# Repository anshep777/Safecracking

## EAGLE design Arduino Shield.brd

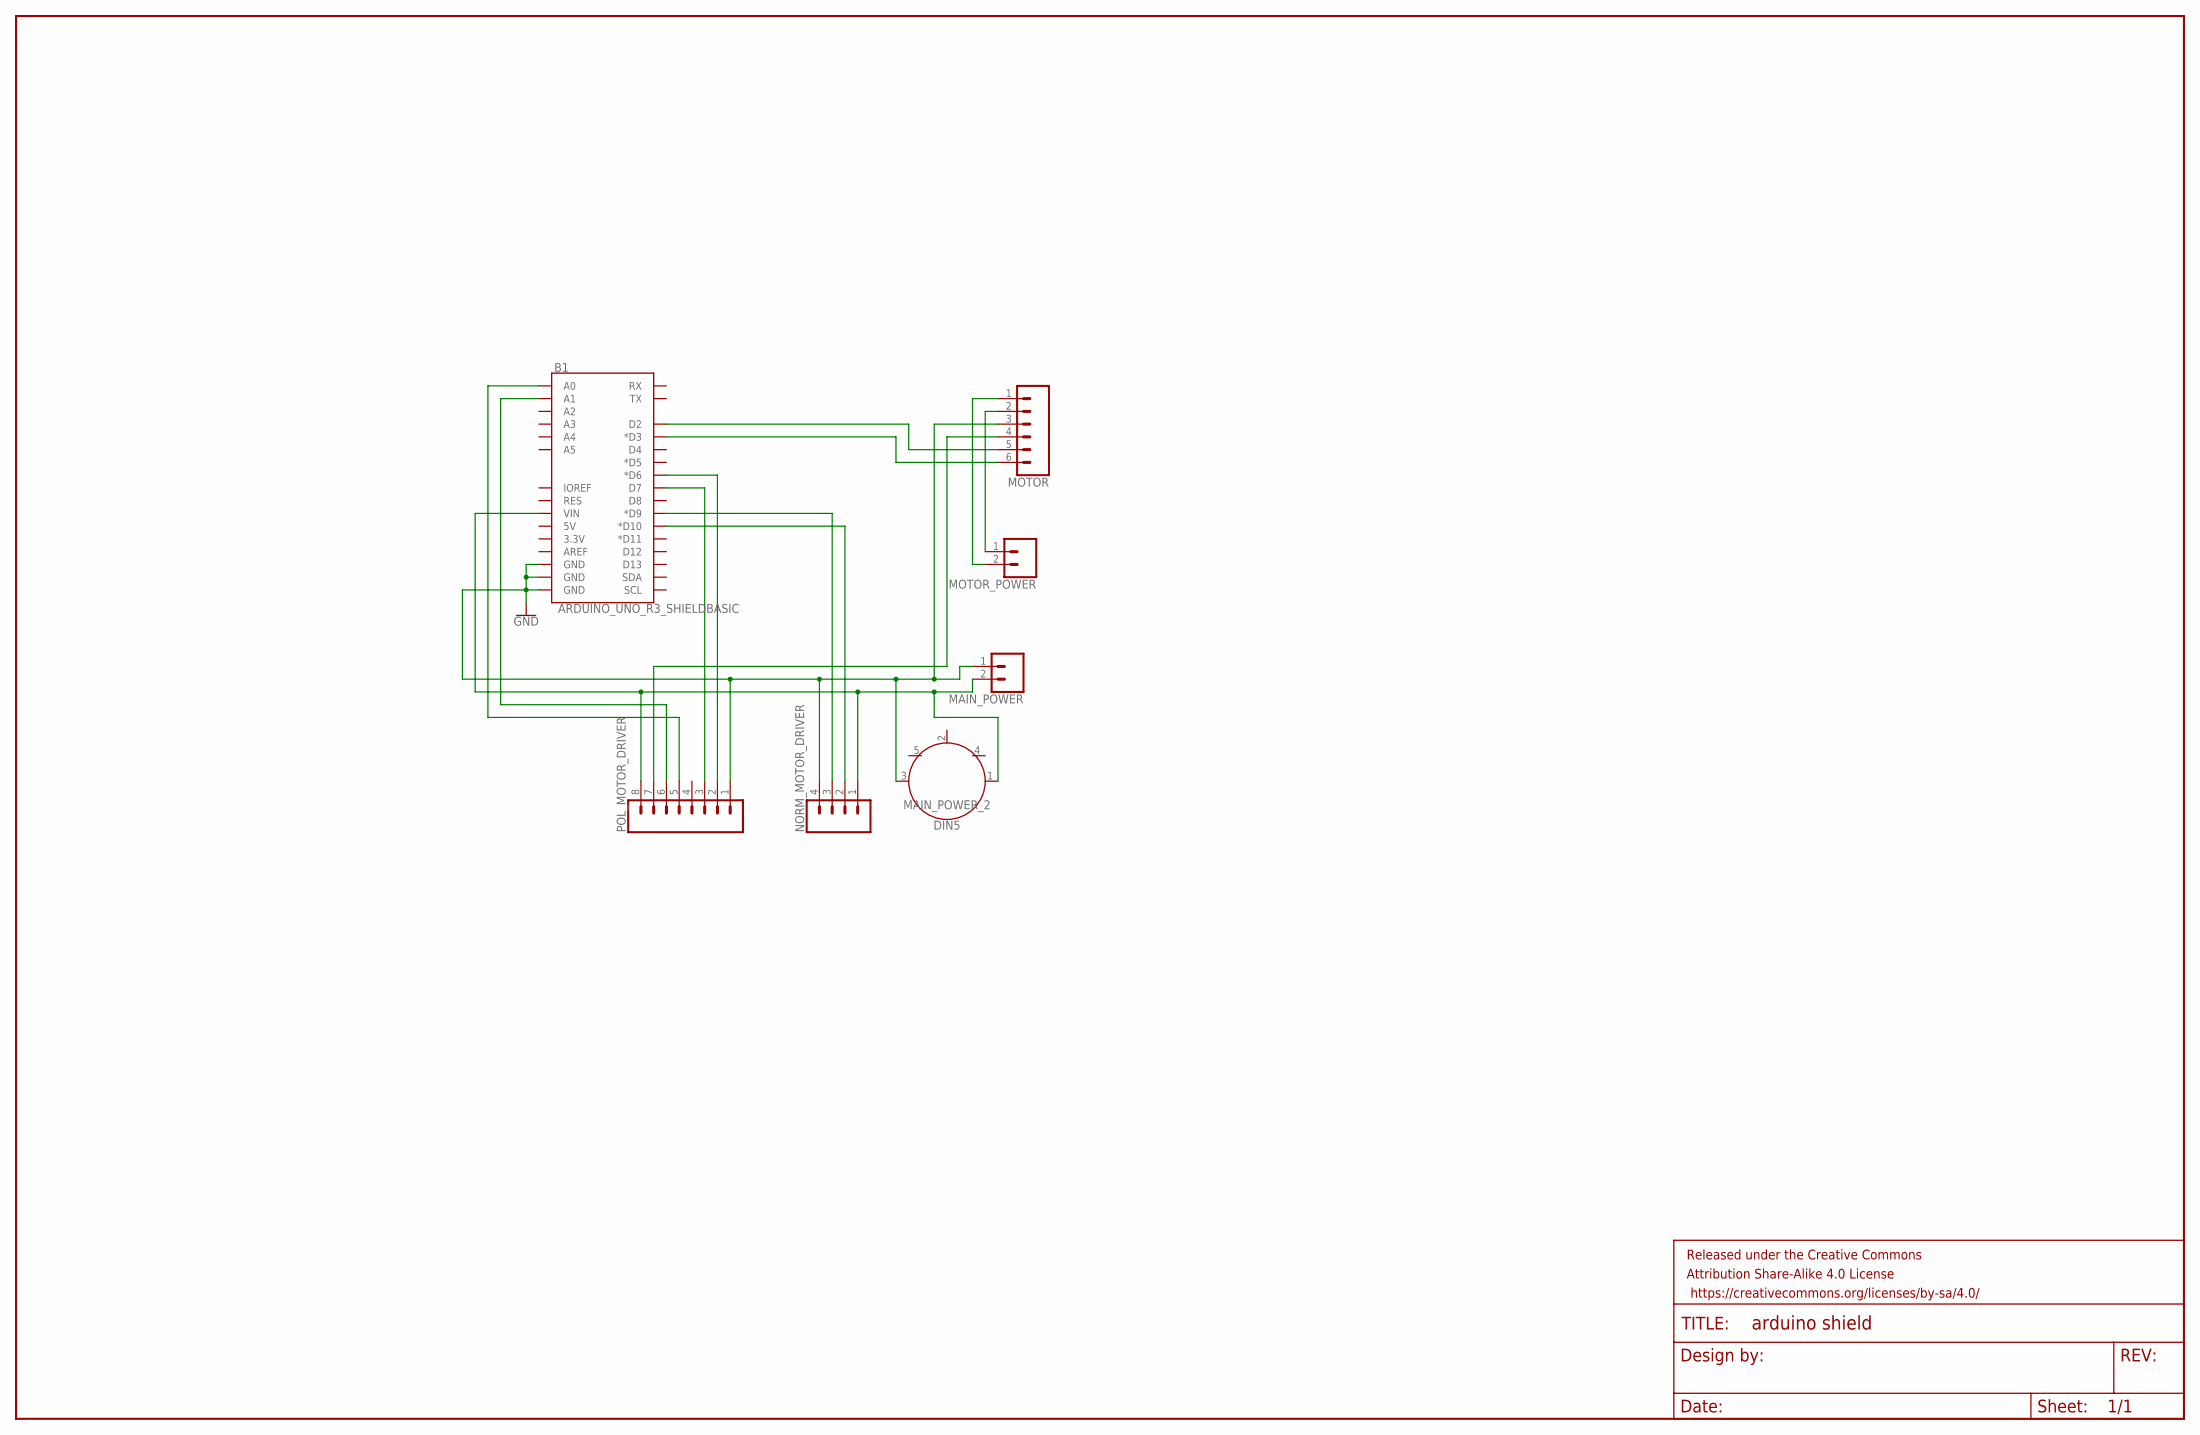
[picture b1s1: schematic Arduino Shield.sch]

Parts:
B1: ARDUINO_UNO_R3_SHIELDBASIC; UNO_R3_SHIELD
FRAME1: FRAME-LEDGER; CREATIVE_COMMONS
MAIN_POWER: CONN_02-JST-2-PTH-NO_SILK; JST-2-PTH-NS
MAIN_POWER_2: DIN5; DIN5-RA-PTH
MOTOR: CONN_06SILK_FEMALE_PTH; 1X06
MOTOR_POWER: CONN_02-JST-2-PTH-NO_SILK; JST-2-PTH-NS
NORM_MOTOR_DRIVER: CONN_04JST-PTH; JST-4-PTH
POL_MOTOR_DRIVER: CONN_08"; 1X08

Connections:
GND: B1.GND@0 (GND), B1.GND@1 (GND), B1.GND@2 (GND), MAIN_POWER.1, MAIN_POWER_2.3, MOTOR.3, NORM_MOTOR_DRIVER.4, POL_MOTOR_DRIVER.1
unnamed: B1.D2, MOTOR.5
unnamed: MOTOR.4, POL_MOTOR_DRIVER.7
unnamed: B1.D3 (*D3), MOTOR.6
unnamed: B1.VIN, MAIN_POWER.2, MAIN_POWER_2.1, NORM_MOTOR_DRIVER.1, POL_MOTOR_DRIVER.8
unnamed: B1.A1, POL_MOTOR_DRIVER.6
unnamed: B1.A0, POL_MOTOR_DRIVER.5
unnamed: B1.D7, POL_MOTOR_DRIVER.3
unnamed: B1.D6 (*D6), POL_MOTOR_DRIVER.2
unnamed: MOTOR.2, MOTOR_POWER.1
unnamed: MOTOR.1, MOTOR_POWER.2
unnamed: B1.D9 (*D9), NORM_MOTOR_DRIVER.3
unnamed: B1.D10 (*D10), NORM_MOTOR_DRIVER.2

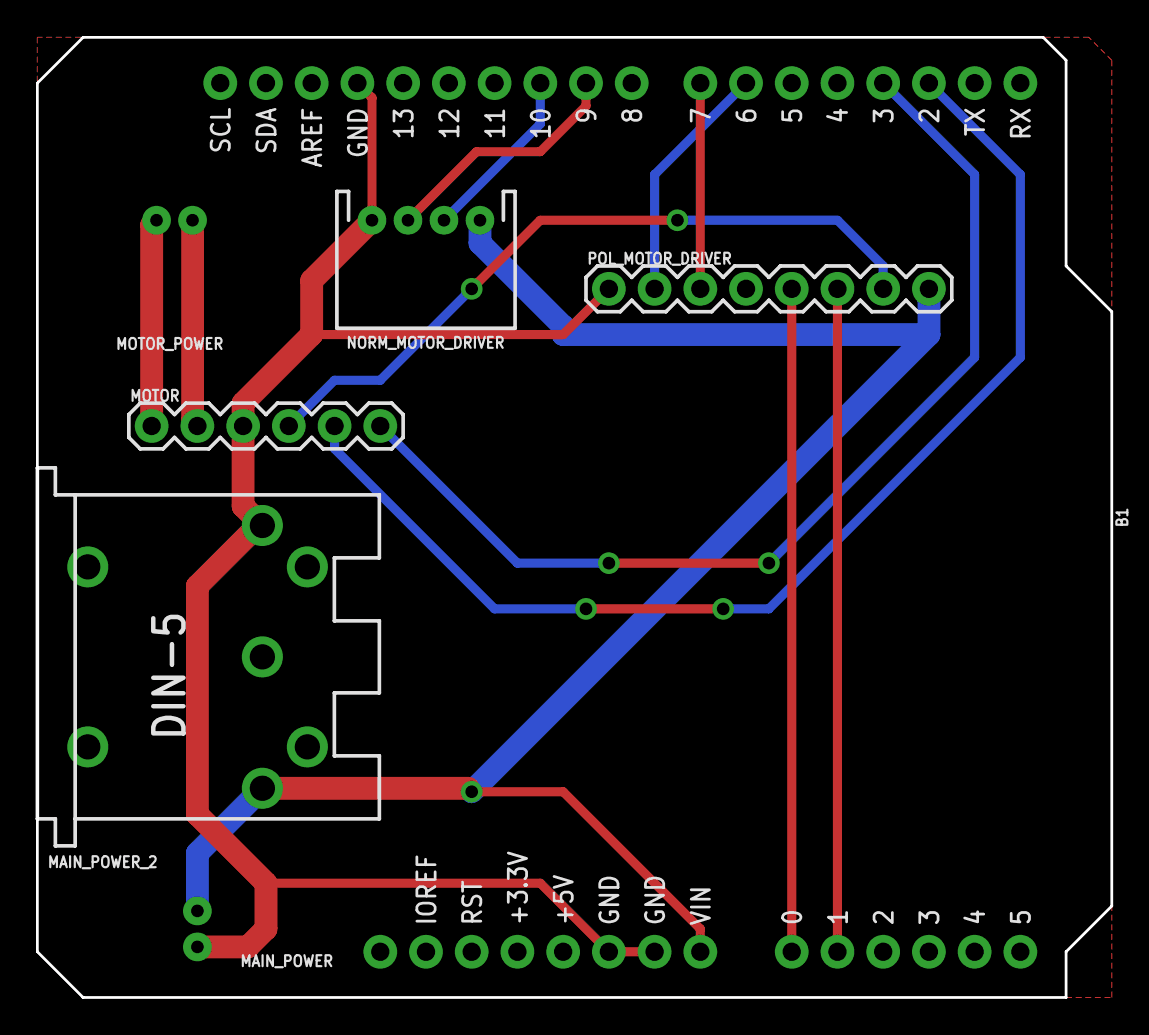
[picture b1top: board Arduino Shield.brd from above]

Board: 2 copper layers, 59.7 x 53.3 mm, 8 parts (0 on the bottom side), 13 nets.

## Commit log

2018-10-24 Update Motor_Enc_with_photogate.ino
    fixed the menu/EEPROM
2018-11-05 Add files via upload
    Code created by superimposing two stepper motor example templates and optimizing the code to run our own stepper motor as fast as possible
2018-11-05 Update Motor_enc_with_EEPROM_slowdown_menu.ino
    Fixed slowDown() funtion so motor doesn't overshoot
2018-11-12 Update safecracking_v1.ino
    fixed goHome and slowDown functions
2018-11-26 Update safecracking_v1.ino
    getting much better
2018-11-27 Update safecracking_v1.ino
    misc changes
2018-11-27 Update safecracking_v1.ino
    eeprom tests
2018-12-03 Update safecracking_v1.ino
    we have one problem: when we change mspeed, the motor stops!
2018-12-05 Update safecracking_v1.ino
    Finally working!! Now to write the cracking algorithm...
2018-12-12 Update safecracking_v1.ino
    not sure which pin servo uses (it's set to 9) but the safecracking algorithm works now for the first two digits. I didn't bother writing code for the third digit because we don't have a handle puller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
2018-12-12 Update safecracking_v1.ino
    fixed typo
2018-12-12 Update safecracking_v1.ino
    added second servo code

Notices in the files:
parts and their libraries:
SparkFun-Boards: Licensing: Creative Commons ShareAlike 4.0 International - https://creativecommons.org/licenses/by-sa/4.0
SparkFun-Aesthetics: Released under the Creative Commons Attribution Share-Alike 4.0 License
SparkFun-Aesthetics: https://creativecommons.org/licenses/by-sa/4.0
